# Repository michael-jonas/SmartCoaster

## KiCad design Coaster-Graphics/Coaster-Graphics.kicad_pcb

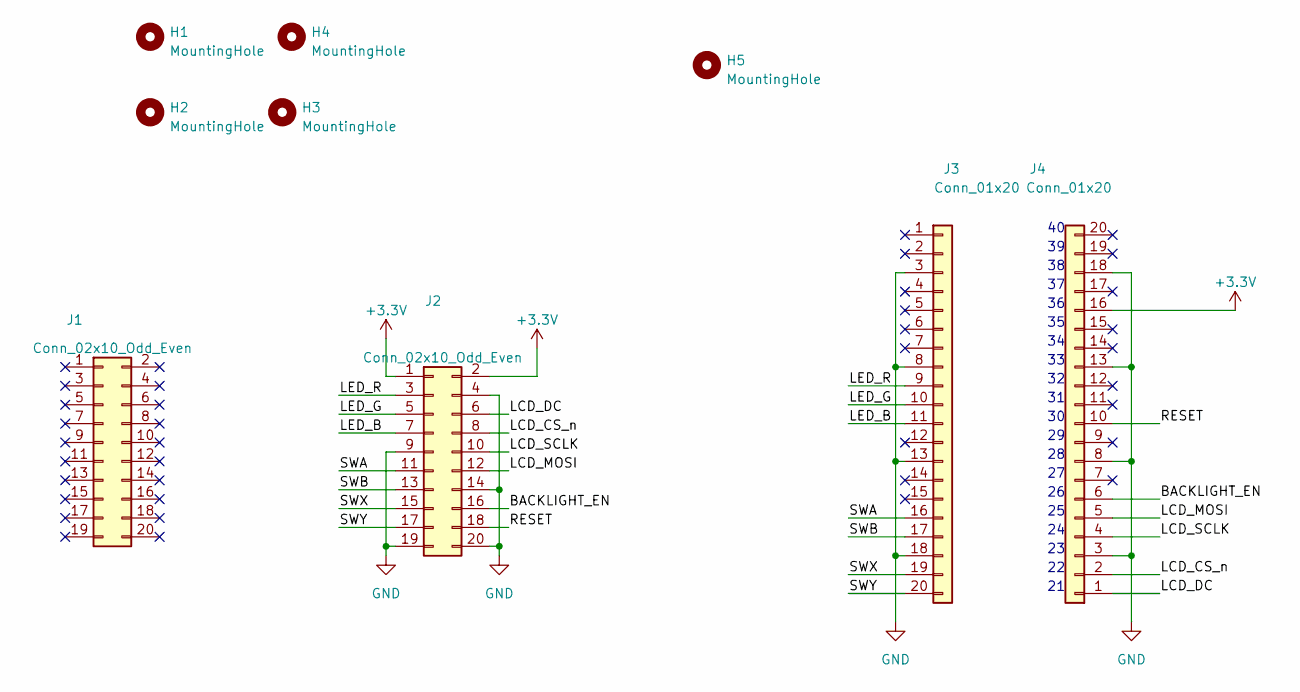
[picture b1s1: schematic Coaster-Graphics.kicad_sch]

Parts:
H1, H2, H3, H4: MountingHole; MountingHole_3.2mm_M3_Pad_TopBottom
H5: MountingHole; MountingHole_4.3mm_M4_ISO14580
J1, J2: Conn_02x10_Odd_Even; HRS_DF12NC_3.0_-20DP-0.5V_51_
J3, J4: Conn_01x20; PinHeader_1x20_P2.54mm_Vertical

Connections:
+3.3V: J2.1, J2.2, J4.16
/BACKLIGHT_EN: J2.16, J4.6
/LCD_CS_n: J2.8, J4.2
/LCD_DC: J2.6, J4.1
/LCD_MOSI: J2.12, J4.5
/LCD_SCLK: J2.10, J4.4
/LED_B: J2.7, J3.11
/LED_G: J2.5, J3.10
/LED_R: J2.3, J3.9
/RESET: J2.18, J4.10
/SWA: J2.11, J3.16
/SWB: J2.13, J3.17
/SWX: J2.15, J3.19
/SWY: J2.17, J3.20
GND: J2.4, J2.9, J2.14, J2.19, J2.20, J3.3, J3.8, J3.13, J3.18, J4.3, J4.8, J4.13, J4.18

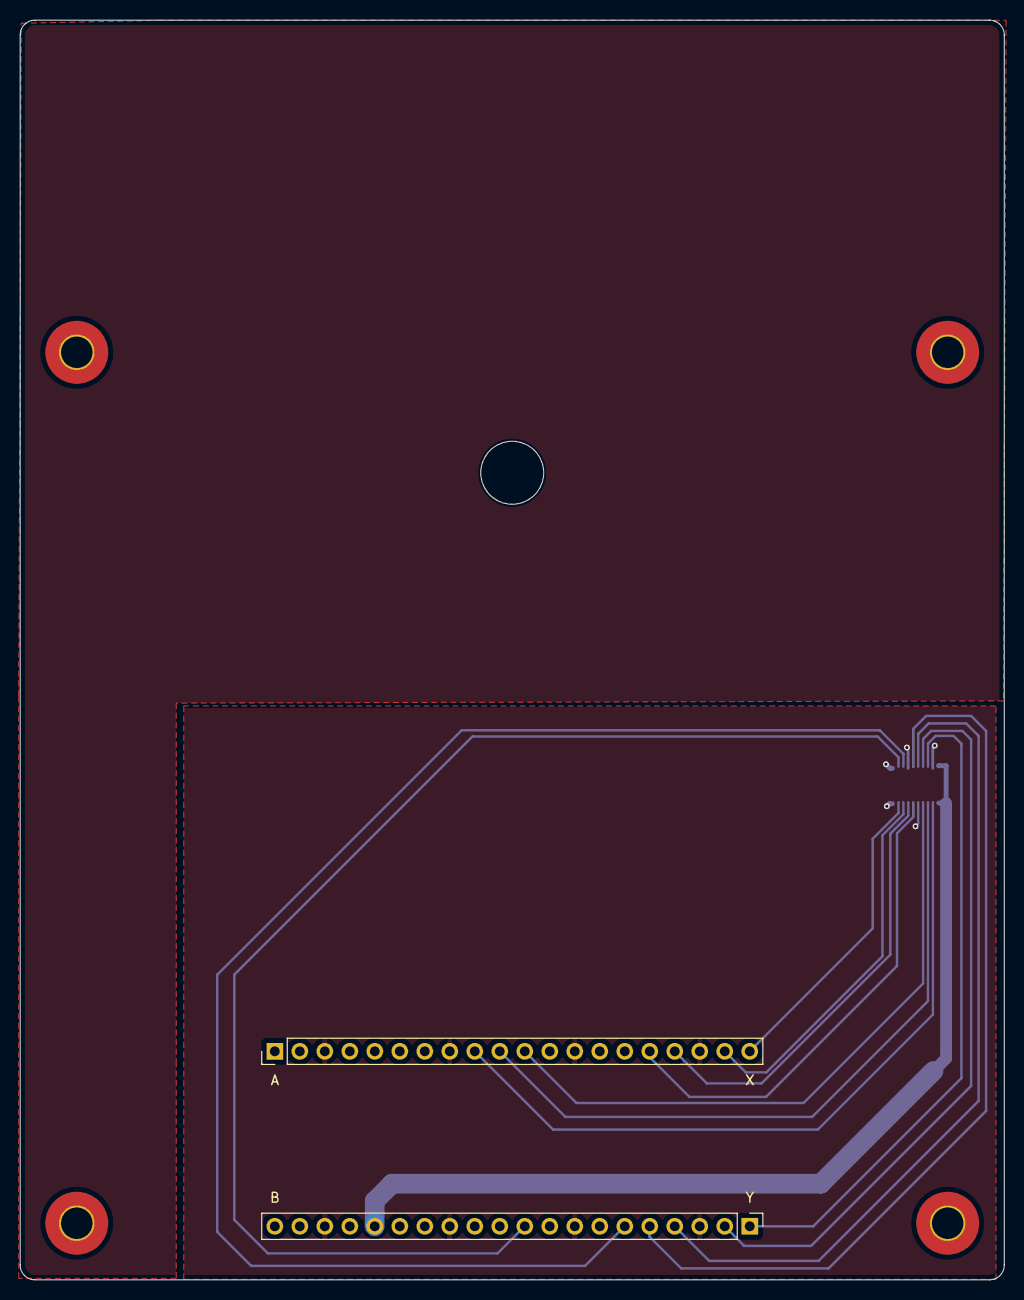
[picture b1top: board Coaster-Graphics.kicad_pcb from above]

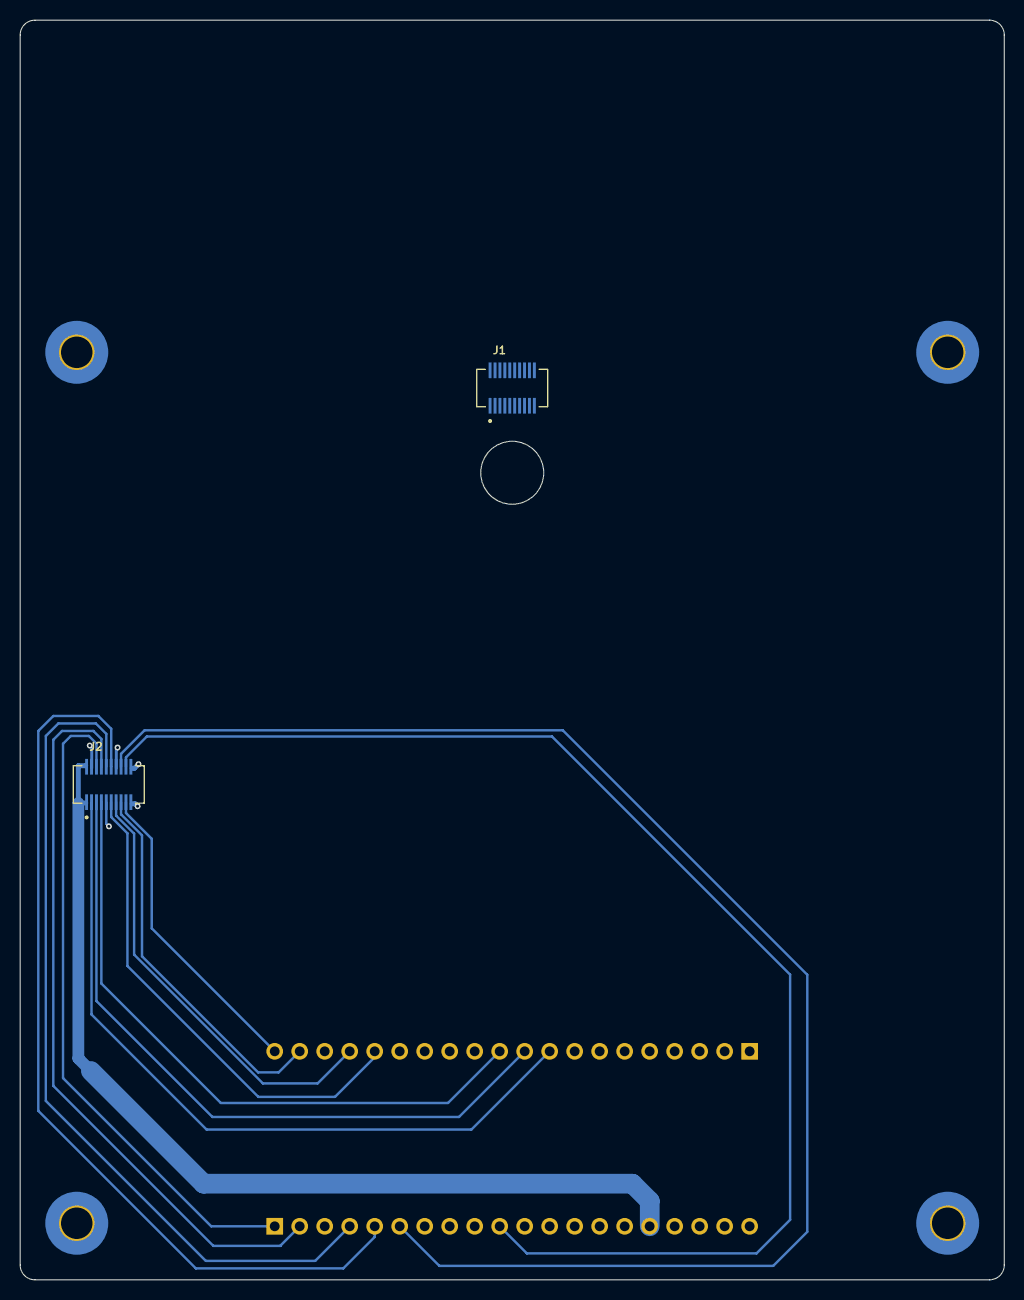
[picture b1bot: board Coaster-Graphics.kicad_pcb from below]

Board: 2 copper layers, 100.0 x 128.0 mm, 9 parts (2 on the bottom side), 15 nets.

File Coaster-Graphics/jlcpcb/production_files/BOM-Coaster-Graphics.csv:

Comment,Designator,Footprint,LCSC
Conn_01x20,J3,PinHeader_1x20_P2.54mm_Vertical,
MountingHole,H4,MountingHole_3.2mm_M3_Pad_TopBottom,
MountingHole,H3,MountingHole_3.2mm_M3_Pad_TopBottom,
MountingHole,H2,MountingHole_3.2mm_M3_Pad_TopBottom,
MountingHole,H1,MountingHole_3.2mm_M3_Pad_TopBottom,
Conn_01x20,J4,PinHeader_1x20_P2.54mm_Vertical,
Conn_02x10_Odd_Even,J2,HRS_DF12NC_3.0_-20DP-0.5V_51_,
Conn_02x10_Odd_Even,J1,HRS_DF12NC_3.0_-20DP-0.5V_51_,

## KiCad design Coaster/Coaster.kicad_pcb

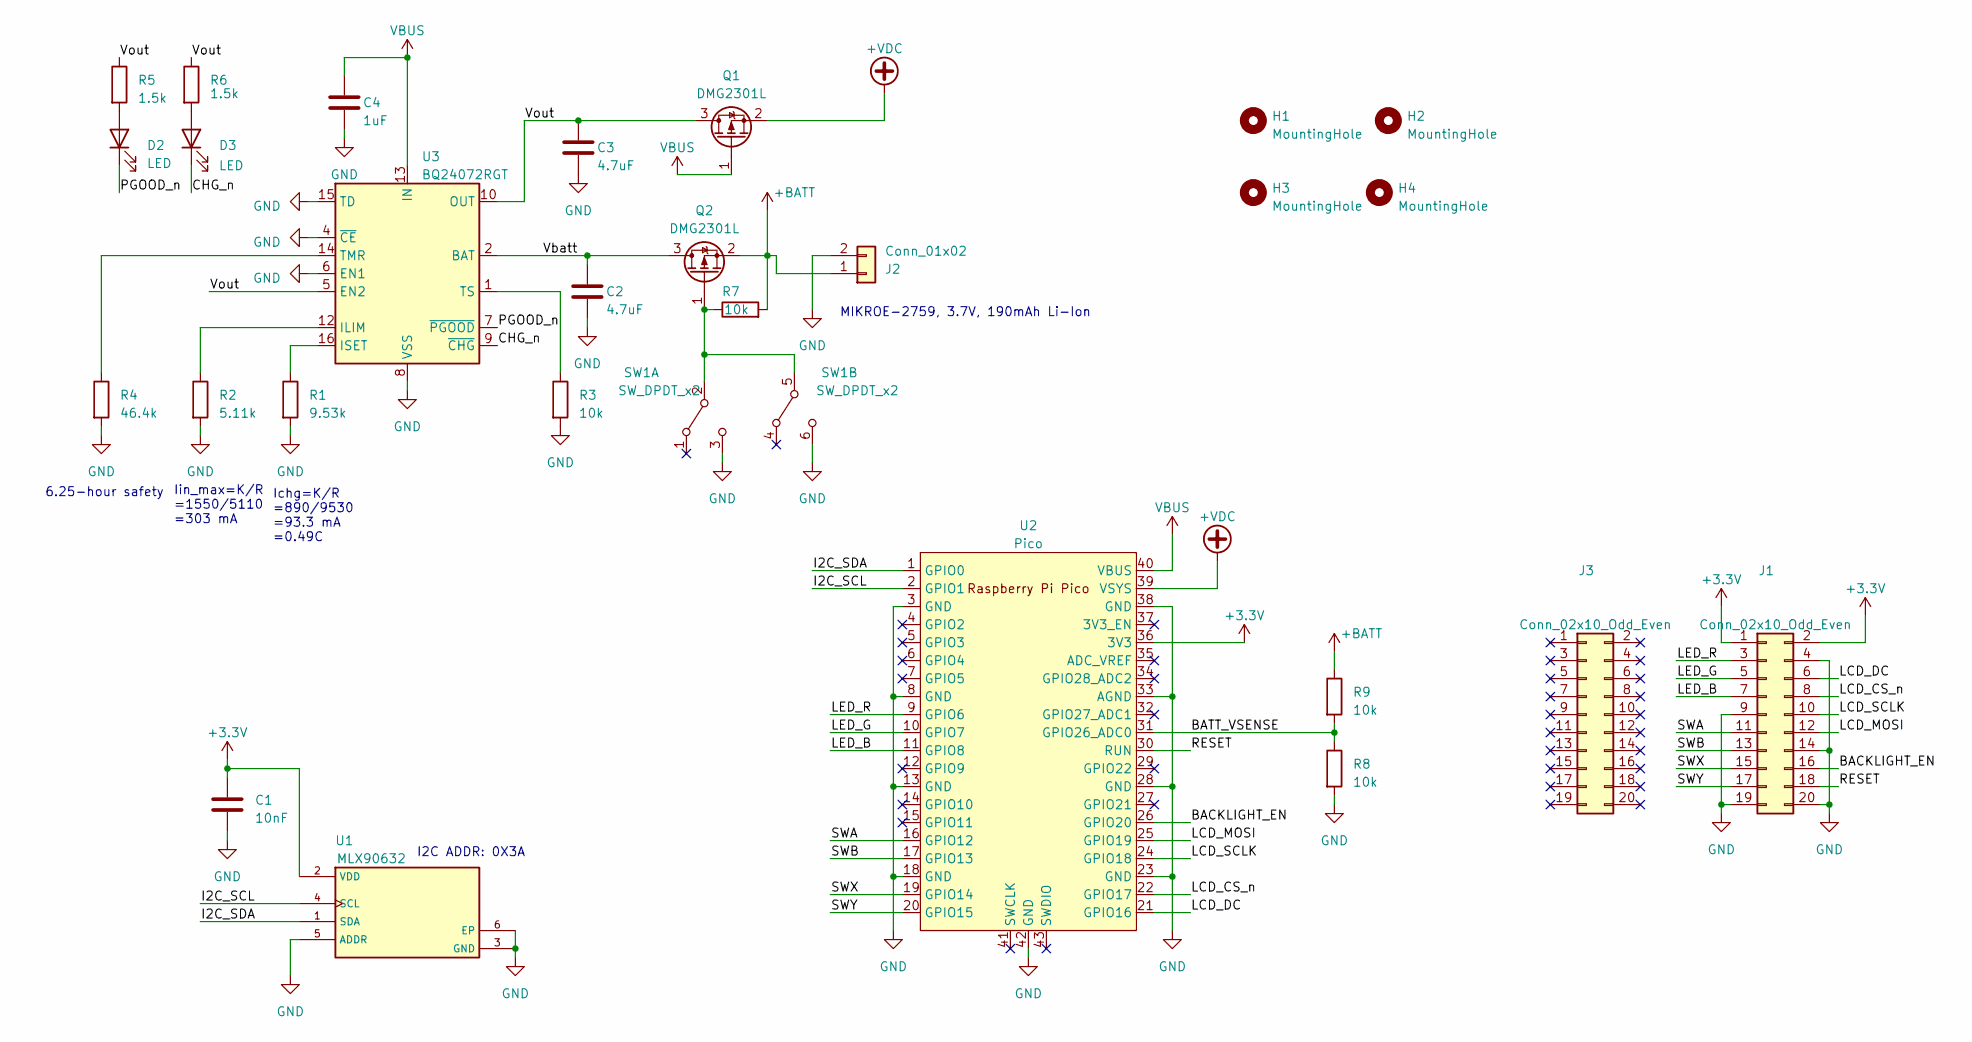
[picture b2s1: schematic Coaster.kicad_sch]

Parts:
C1: 10nF; C_0603_1608Metric
C2, C3: 4.7uF; C_0603_1608Metric
C4: 1uF; C_0603_1608Metric
D2, D3: LED; LED_0603_1608Metric
H1, H2, H3, H4: MountingHole; MountingHole_3.2mm_M3_Pad_TopBottom
J1, J3: Conn_02x10_Odd_Even; HRS_DF12NC-20DS-0.5V_51_
J2: Conn_01x02; JST_SH_SM02B-SRSS-TB_1x02-1MP_P1.00mm_Horizontal
Q1, Q2: DMG2301L; SOT-23
R1: 9.53k; R_0603_1608Metric
R2: 5.11k; R_0603_1608Metric
R3, R7, R8, R9: 10k; R_0603_1608Metric
R4: 46.4k; R_0603_1608Metric
R5, R6: 1.5k; R_0603_1608Metric
SW1: SW_DPDT_x2; K3-2245S
U1: MLX90632; XDCR_MLX90632SLD-BCB-000-SP
U2: Pico; RPi_Pico_SMD_TH
U3: BQ24072RGT; VQFN-16-1EP_3x3mm_P0.5mm_EP1.6x1.6mm

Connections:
+3.3V: C1.1, J1.1, J1.2, U1.2 (VDD), U2.36 (3V3)
+BATT: J2.1, Q2.2 (S), R7.2, R9.1
+VDC: Q1.2 (S), U2.39 (VSYS)
/BACKLIGHT_EN: J1.16, U2.26 (GPIO20)
/BATT_VSENSE: R8.1, R9.2, U2.31 (GPIO26_ADC0)
/CHG_n: D3.1 (K), U3.9 (~CHG)
/I2C_SCL: U1.4 (SCL), U2.2 (GPIO1)
/I2C_SDA: U1.1 (SDA), U2.1 (GPIO0)
/LCD_CS_n: J1.8, U2.22 (GPIO17)
/LCD_DC: J1.6, U2.21 (GPIO16)
/LCD_MOSI: J1.12, U2.25 (GPIO19)
/LCD_SCLK: J1.10, U2.24 (GPIO18)
/LED_B: J1.7, U2.11 (GPIO8)
/LED_G: J1.5, U2.10 (GPIO7)
/LED_R: J1.3, U2.9 (GPIO6)
/PGOOD_n: D2.1 (K), U3.7 (~PGOOD)
/RESET: J1.18, U2.30 (RUN)
/SWA: J1.11, U2.16 (GPIO12)
/SWB: J1.13, U2.17 (GPIO13)
/SWX: J1.15, U2.19 (GPIO14)
/SWY: J1.17, U2.20 (GPIO15)
/Vbatt: C2.1, Q2.3 (D), U3.2 (BAT), U3.3 (BAT)
/Vout: C3.1, Q1.3 (D), R5.1, R6.1, U3.5 (EN2), U3.10 (OUT), U3.11 (OUT)
GND: C1.2, C2.2, C3.2, C4.2, J1.4, J1.9, J1.14, J1.19, J1.20, J2.2, R1.2, R2.2, R3.2, R4.2, R8.2, SW1.3 (C), SW1.6 (C), U1.3 (GND), U1.5 (ADDR), U1.6 (EP), U2.3 (GND), U2.8 (GND), U2.13 (GND), U2.18 (GND), U2.23 (GND), U2.28 (GND), U2.33 (AGND), U2.38 (GND), U2.42 (GND), U3.4 (~CE), U3.6 (EN1), U3.8 (VSS), U3.15 (TD), U3.17 (VSS)
unnamed: D2.2 (A), R5.2
unnamed: D3.2 (A), R6.2
unnamed: Q2.1 (G), R7.1, SW1.2 (B), SW1.5 (B)
unnamed: R2.1, U3.12 (ILIM)
unnamed: R1.1, U3.16 (ISET)
unnamed: R4.1, U3.14 (TMR)
unnamed: R3.1, U3.1 (TS)
VBUS: C4.1, Q1.1 (G), U2.40 (VBUS), U3.13 (IN)

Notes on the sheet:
Iin_max=K/R =1550/5110 =303 mA
Ichg=K/R =890/9530 =93.3 mA =0.49C
6.25-hour safety
MIKROE-2759, 3.7V, 190mAh Li-Ion
I2C ADDR: 0X3A

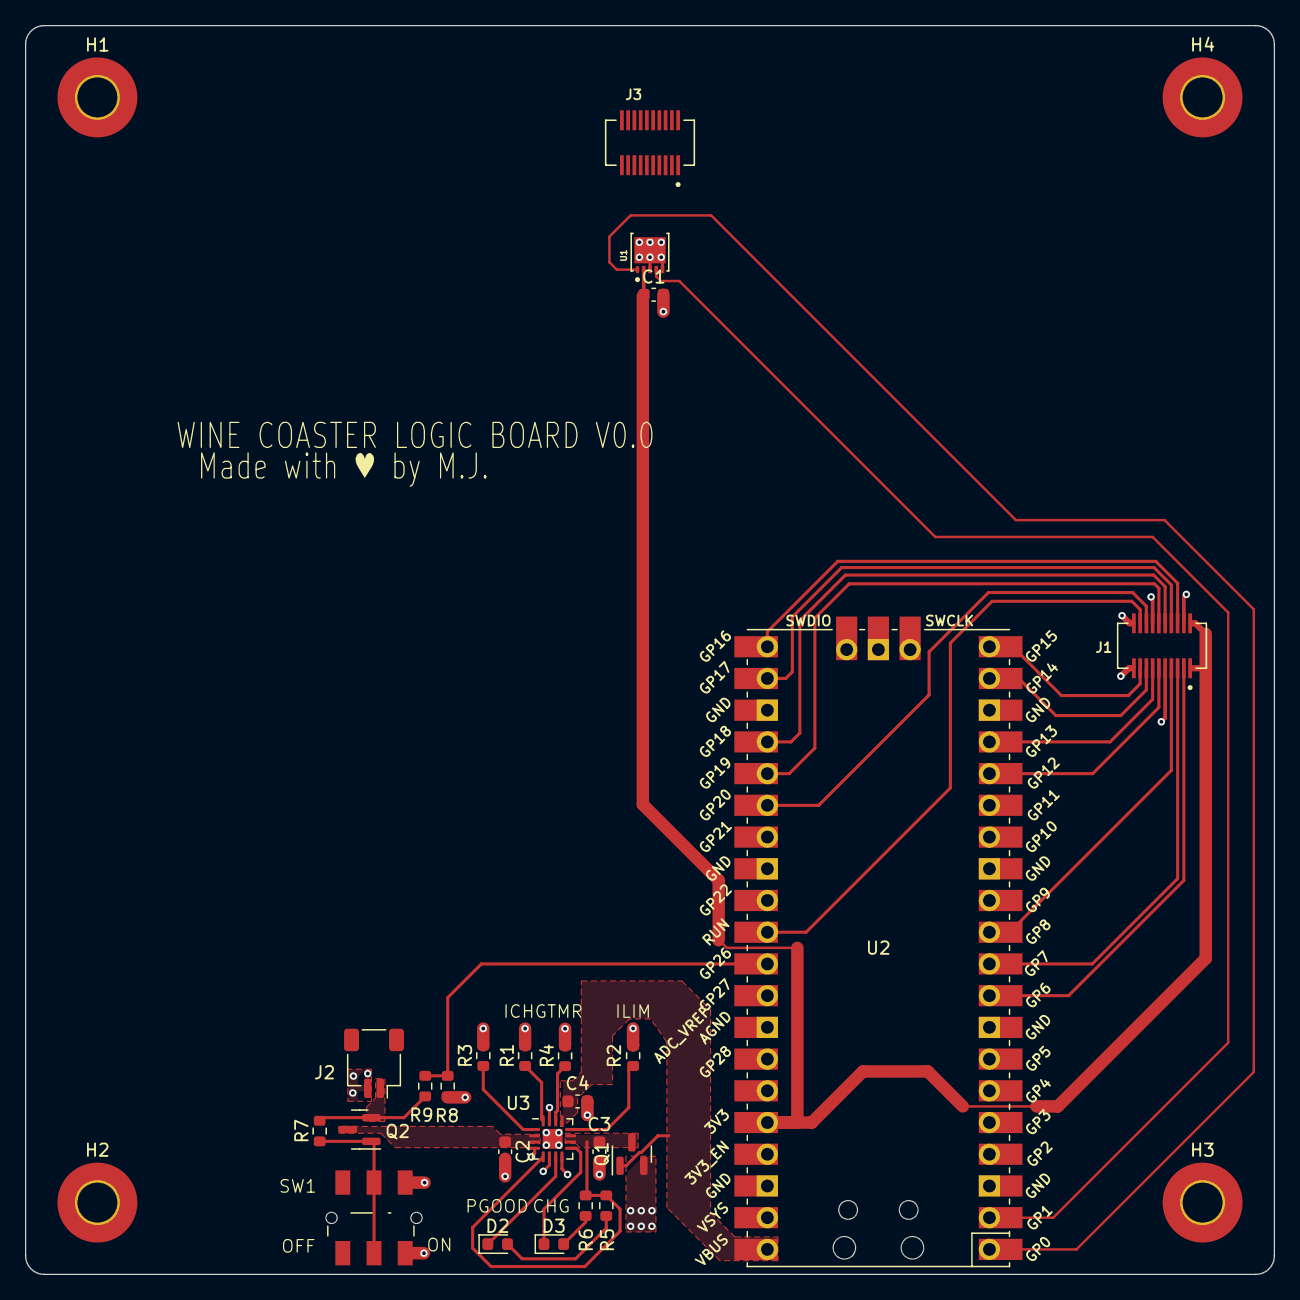
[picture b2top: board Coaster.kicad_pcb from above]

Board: 2 copper layers, 100.0 x 100.0 mm, 28 parts (0 on the bottom side), 32 nets.

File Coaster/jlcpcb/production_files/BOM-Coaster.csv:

Comment,Designator,Footprint,LCSC
5.11k,R2,R_0603_1608Metric,C112314
BQ24072RGT,U3,VQFN-16-1EP_3x3mm_P0.5mm_EP1.6x1.6mm,C140288
DMG2301L,"Q1,Q2",SOT-23,C144153
1uF,C4,C_0603_1608Metric,C15849
Conn_01x02,J2,JST_SH_SM02B-SRSS-TB_1x02-1MP_P1.00mm_Horizontal,C160402
46.4k,R4,R_0603_1608Metric,C165747
SW_DPDT_x2,SW1,K3-2245S,C223861
9.53k,R1,R_0603_1608Metric,C228113
1.5k,"R5,R6",R_0603_1608Metric,C22843
Conn_02x10_Odd_Even,"J1,J3",HRS_DF12NC-20DS-0.5V_51_,C3645324
LED,"D2,D3",LED_0603_1608Metric,C510026
MLX90632,U1,XDCR_MLX90632SLD-BCB-000-SP,C5209729
Pico,U2,RPi_Pico_SMD_TH,C7203002
10nF,C1,C_0603_1608Metric,C7248
4.7uF,"C2,C3",C_0603_1608Metric,C90057
10k,"R3,R7,R8,R9",R_0603_1608Metric,C98220
MountingHole,H4,MountingHole_3.2mm_M3_Pad_TopBottom,
MountingHole,H3,MountingHole_3.2mm_M3_Pad_TopBottom,
MountingHole,H2,MountingHole_3.2mm_M3_Pad_TopBottom,
MountingHole,H1,MountingHole_3.2mm_M3_Pad_TopBottom,

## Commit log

2023-12-11 Initial commit.
2023-12-11 second commit
2023-12-11 Added software folder.
2023-12-17 Push some software testing.
